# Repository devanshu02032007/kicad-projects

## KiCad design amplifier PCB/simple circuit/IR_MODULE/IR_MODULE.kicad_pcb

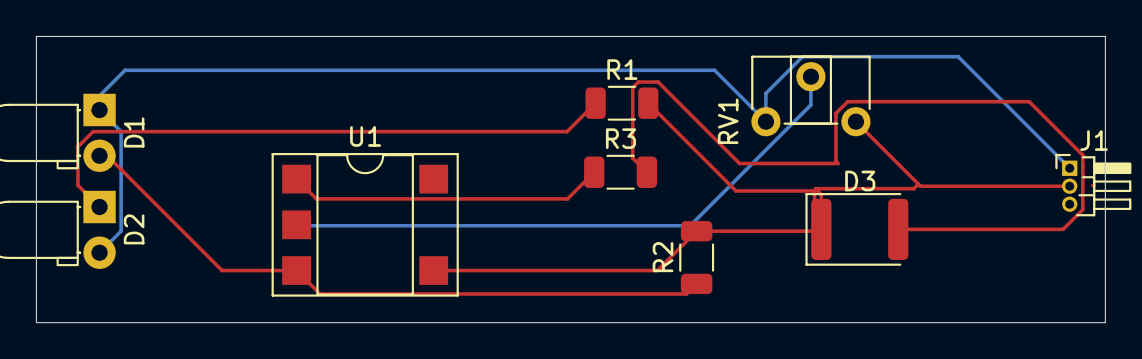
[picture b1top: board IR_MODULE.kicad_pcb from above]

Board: 2 copper layers, 59.4 x 15.9 mm, 9 parts (0 on the bottom side), 7 nets.

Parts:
D1, D2: LED; LED_D3.0mm_Horizontal_O1.27mm_Z2.0mm
D3: LED; LED_1812_4532Metric
J1: POWERCON; PinHeader_1x03_P1.00mm_Horizontal
R1: 100; R_1206_3216Metric
R2: 10K; R_1206_3216Metric
R3: 330; R_1206_3216Metric
RV1: 10K; Potentiometer_ACP_CA6-H2,5_Horizontal
U1: LM358; DIP-5-6_W7.62mm_SMDSocket_SmallPads

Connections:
+5V: D1.1 (K), D2.2 (A), J1.1, RV1.1
/OUT: D3.2 (A), R3.2
GND: D3.1 (K), J1.2, R1.2, R2.2, RV1.3, U1.4 (V-)
unnamed: D1.2 (A), R2.1, U1.3 (+)
unnamed: D2.1 (K), R1.1
unnamed: R3.1, U1.1
unnamed: RV1.2, U1.2 (-)

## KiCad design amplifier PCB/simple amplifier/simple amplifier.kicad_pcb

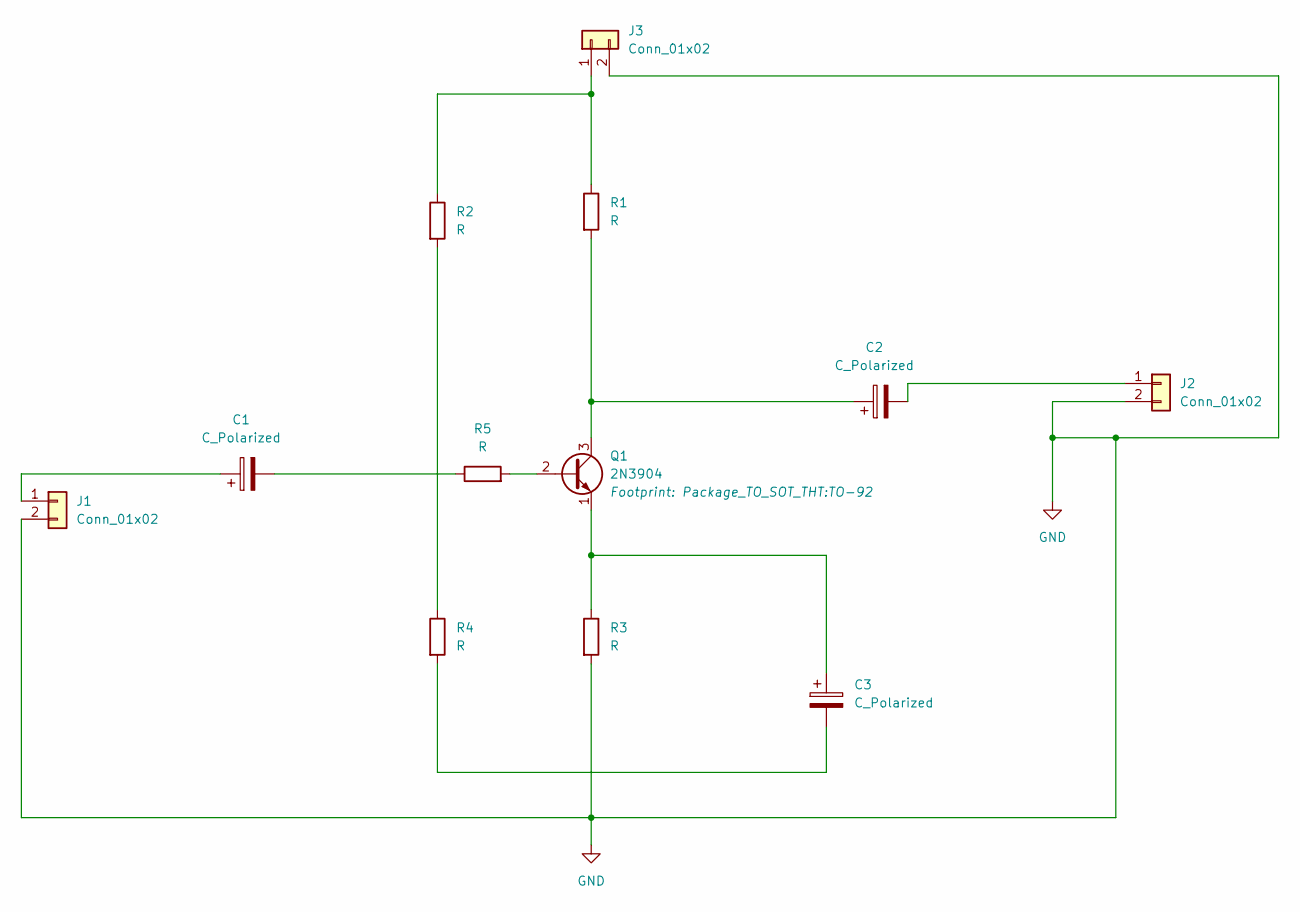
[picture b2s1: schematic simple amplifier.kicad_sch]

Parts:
C1, C2, C3: C_Polarized; CP_Elec_10x10
J1, J2, J3: Conn_01x02; AMASS_XT30PW-F_1x02_P2.50mm_Horizontal
Q1: 2N3904; TO-92
R1: R; R_Axial_DIN0204_L3.6mm_D1.6mm_P5.08mm_Horizontal
R2, R3, R4, R5: R; R_01005_0402Metric_Pad0.57x0.30mm_HandSolder

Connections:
GND: J1.2, J2.2, J3.2, R3.2
unnamed: C1.2, R5.1
unnamed: C3.2, R4.2
unnamed: C1.1, J1.1
unnamed: C2.2, J2.1
unnamed: J3.1, R1.1, R2.1
unnamed: Q1.2 (B), R5.2
unnamed: C2.1, Q1.3 (C), R1.2
unnamed: C3.1, Q1.1 (E), R3.1
unnamed: R2.2, R4.1

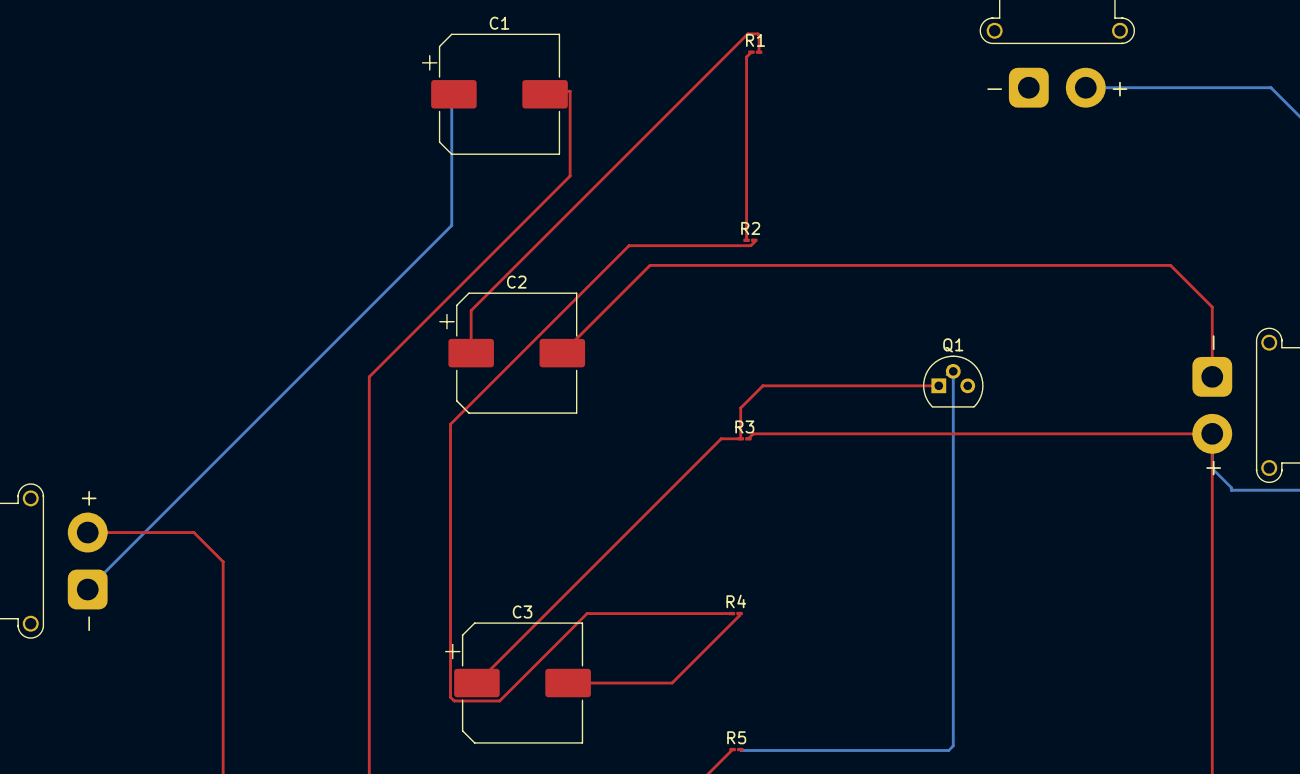
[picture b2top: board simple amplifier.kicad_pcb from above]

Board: 2 copper layers, 12 parts (0 on the bottom side), 10 nets.
